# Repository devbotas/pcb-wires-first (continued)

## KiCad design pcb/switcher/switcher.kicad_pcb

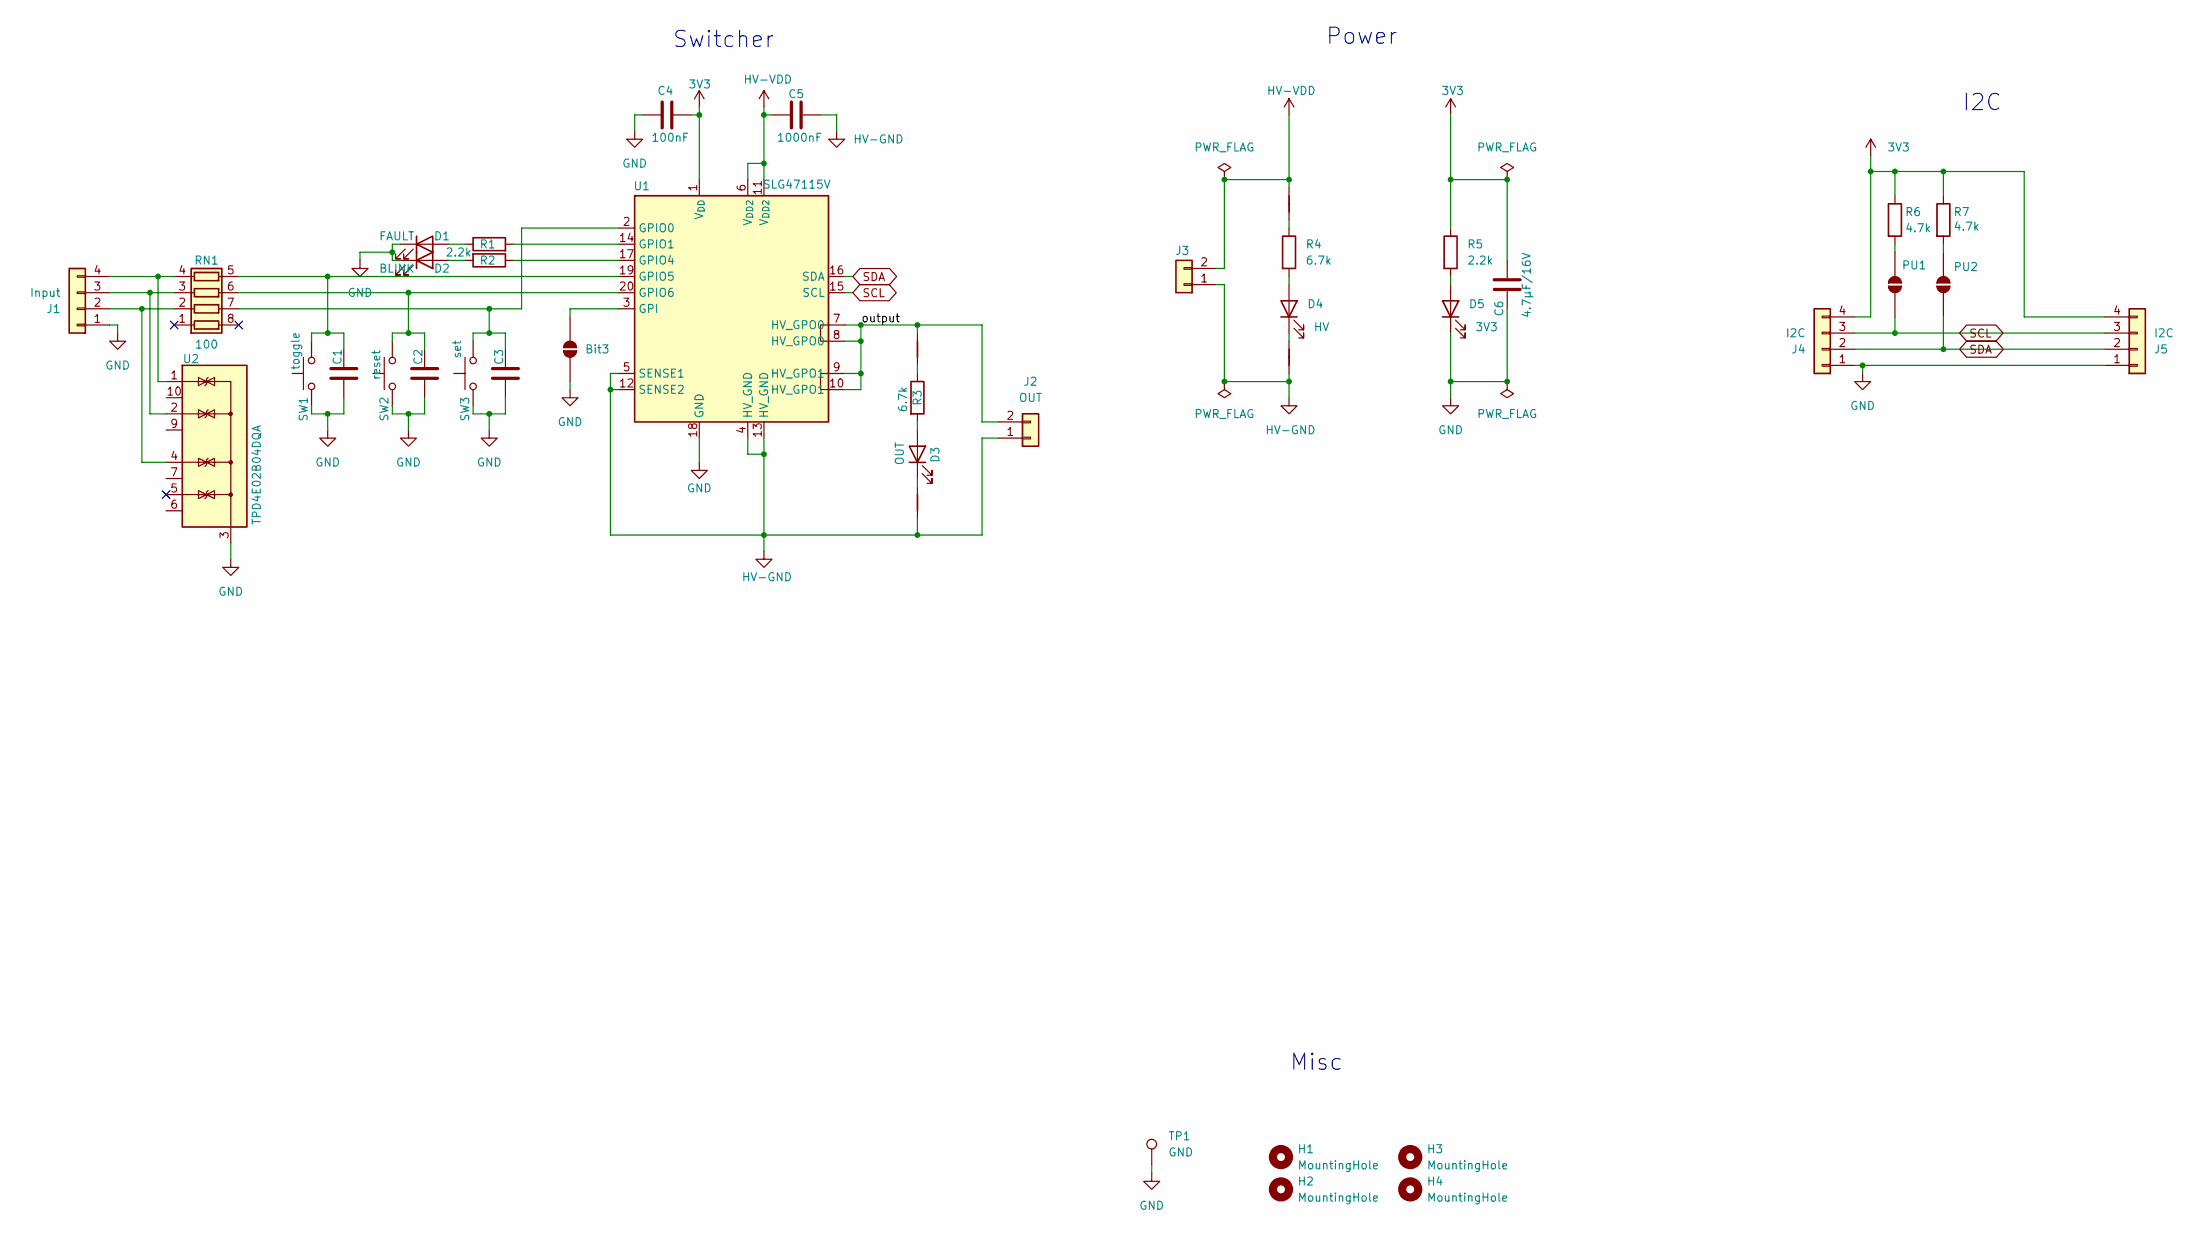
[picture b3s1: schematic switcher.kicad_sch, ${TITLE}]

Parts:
Bit3: SolderJumper_2_Open; SolderJumper-2_P1.3mm_Open_RoundedPad1.0x1.5mm
C1, C2, C3, C4: 100nF; C_0603_1608Metric
C5: 1000nF; C_0603_1608Metric
C6: 4.7μF/16V; C_0603_1608Metric
D1: FAULT; D_0603_1608Metric
D2: BLINK; D_0603_1608Metric
D3: OUT; D_0603_1608Metric
D4: HV; D_0603_1608Metric
D5: 3V3; D_0603_1608Metric
H1, H2, H3, H4: MountingHole; MountingHole_3.2mm_M3_NoCopper
J1: Input; PhoenixContact_MCV_1,5_4-G-3.5_1x04_P3.50mm_Vertical
J2: OUT; JST_VH_B2P-VH_1x02_P3.96mm_Vertical
J3: Conn_01x02; JST_VH_B2P-VH_1x02_P3.96mm_Vertical
J4, J5: I2C; JST_XH_B4B-XH-A_1x04_P2.50mm_Vertical
NT1, NT3, NT4: NetTie_2; NetTie-2_SMD_Pad0.5mm
NT2: NetTie_2; NetTie-2_THT_Pad0.3mm
PU1, PU2: SolderJumper_2_Open; SolderJumper-2_P1.3mm_Open_RoundedPad1.0x1.5mm
R1, R2, R5: 2.2k; R_0603_1608Metric
R3, R4: 6.7k; R_0603_1608Metric
R6, R7: 4.7k; R_0603_1608Metric
RN1: 100; R_Array_Concave_4x0603
SW1: toggle; SW_SPST_B3U-1000P
SW2: reset; SW_SPST_B3U-1000P
SW3: set; SW_SPST_B3U-1000P
TP1: GND; TestPoint_Keystone_5019_Miniature
U1: SLG47115V; Renesas_UQFN-20_2x3mm_P0.4mm_SLG47115V
U2: TPD4E02B04DQA; USON-10_2.5x1.0mm_P0.5mm

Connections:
3V3: C4.2, C6.1, J4.4, J5.4, R5.1, R6.1, R7.1, U1.1 (V_{DD})
/output: J2.2, NT1.2, U1.7 (HV_GPO0), U1.8 (HV_GPO0), U1.9 (HV_GPO1), U1.10 (HV_GPO1)
GND: Bit3.1 (A), C1.1, C2.1, C3.1, C4.1, C6.2, D1.1 (K), D2.1 (K), D5.1 (K), J1.1, J4.1, J5.1, SW1.1, SW2.1, SW3.1, TP1.1 (1_1), U1.18 (GND), U2.3 (G), U2.8 (G)
HV-GND: C5.1, J2.1, J3.1, NT2.1, NT4.1, U1.4 (HV_GND), U1.5 (SENSE1), U1.12 (SENSE2), U1.13 (HV_GND)
HV-VDD: C5.2, J3.2, NT3.2, U1.6 (V_{DD2}), U1.11 (V_{DD2})
unnamed: Bit3.2 (B), U1.3 (GPI)
unnamed: D1.2 (A), R1.1
unnamed: D2.2 (A), R2.2
unnamed: D3.2 (A), R3.2
unnamed: D3.1 (K), NT2.2
unnamed: D4.2 (A), R4.2
unnamed: D4.1 (K), NT4.2
unnamed: D5.2 (A), R5.2
unnamed: J1.2, RN1.2 (R2.1), U2.4 (IO3)
unnamed: J1.3, RN1.3 (R3.1), U2.2 (IO2)
unnamed: J1.4, RN1.4 (R4.1), U2.1 (IO1)
unnamed: NT1.1, R3.1
unnamed: NT3.1, R4.1
unnamed: PU1.2 (B), R6.2
unnamed: PU2.2 (B), R7.2
unnamed: C3.2, RN1.7 (R2.2), SW3.2, U1.2 (GPIO0)
unnamed: C2.2, RN1.6 (R3.2), SW2.2, U1.20 (GPIO6)
unnamed: C1.2, RN1.5 (R4.2), SW1.2, U1.19 (GPIO5)
unnamed: R1.2, U1.14 (GPIO1)
unnamed: R2.1, U1.17 (GPIO4)
SCL: J4.3, J5.3, PU1.1 (A), U1.15 (SCL)
SDA: J4.2, J5.2, PU2.1 (A), U1.16 (SDA)

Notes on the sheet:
Switcher
I2C
Power
Misc

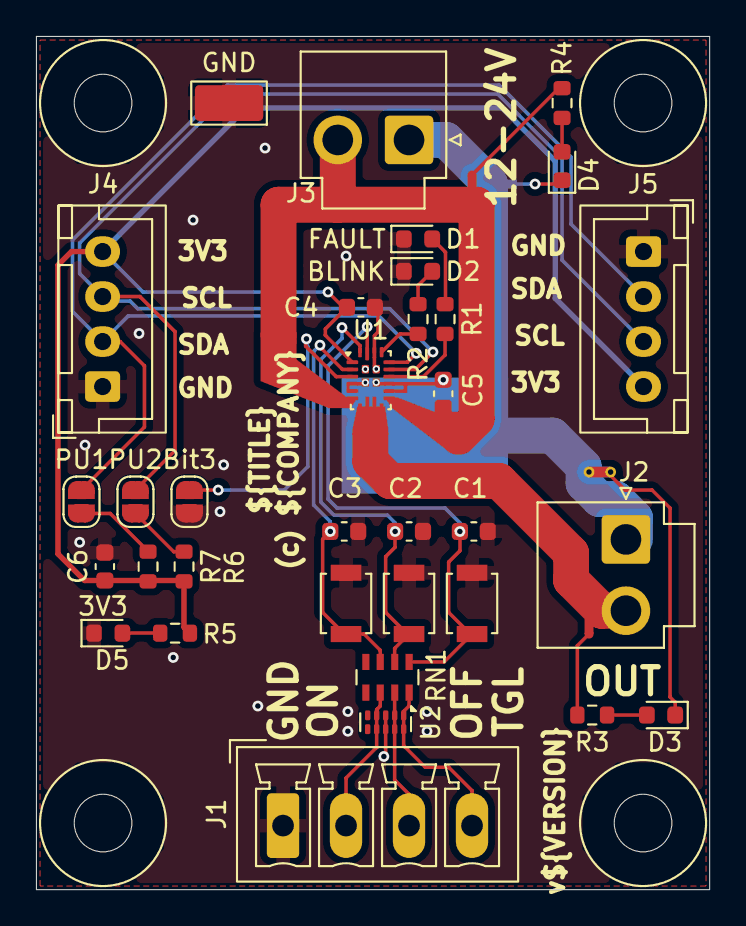
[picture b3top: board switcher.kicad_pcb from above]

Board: 2 copper layers, 37.4 x 47.4 mm, 41 parts (1 on the bottom side), 27 nets.

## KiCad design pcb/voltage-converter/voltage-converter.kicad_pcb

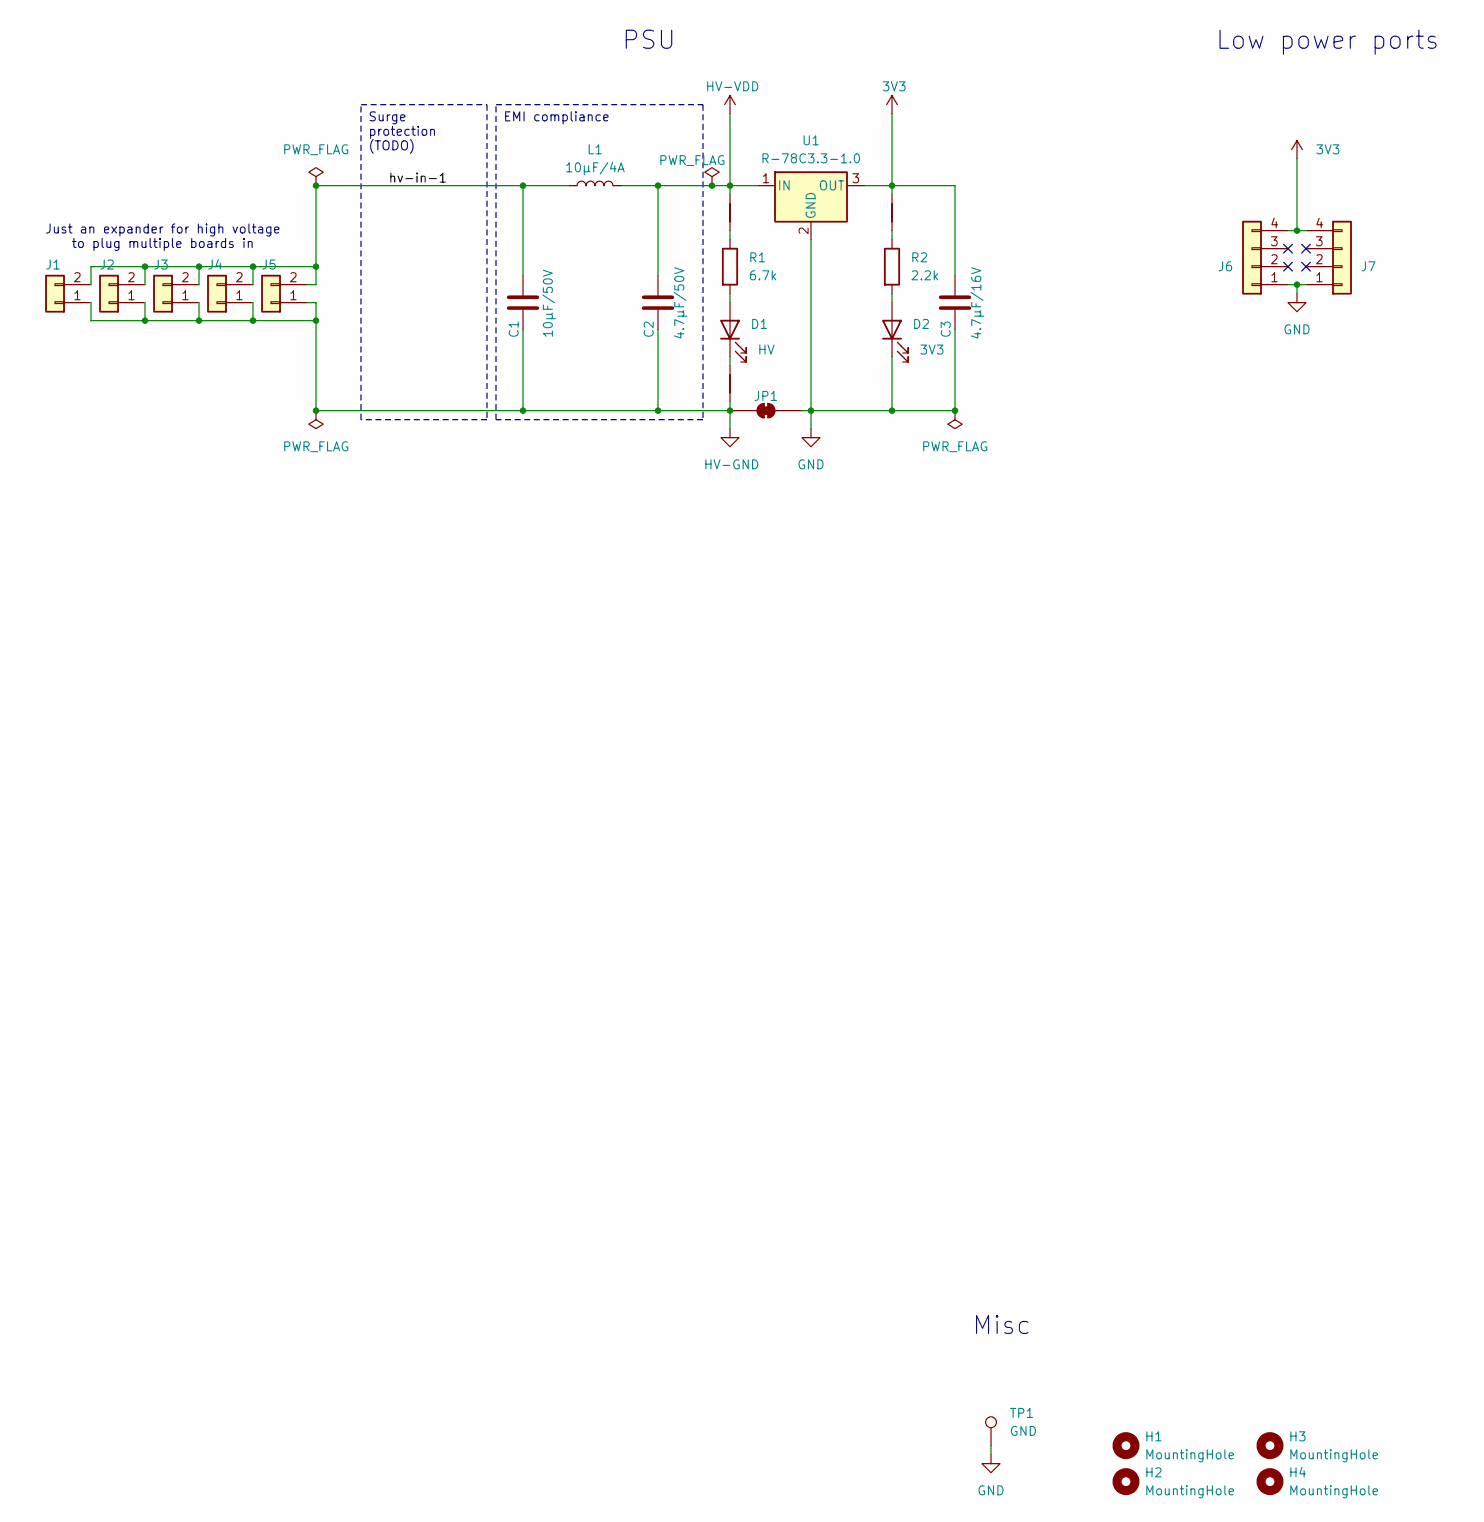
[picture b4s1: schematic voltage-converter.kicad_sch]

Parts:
C1: 10μF/50V; C_1206_3216Metric
C2: 4.7μF/50V; C_1206_3216Metric
C3: 4.7μF/16V; C_0603_1608Metric
D1: HV; D_0603_1608Metric
D2: 3V3; D_0603_1608Metric
H1, H2, H3, H4: MountingHole; MountingHole_3.2mm_M3_NoCopper
J1, J2, J3, J4, J5: Conn_01x02; JST_VH_B2P-VH_1x02_P3.96mm_Vertical
J6, J7: JST_XH_B4B-XH-A_1x04_P2.50mm_Vertical
JP1: SolderJumper_2_Bridged; SolderJumper-2_P1.3mm_Bridged_RoundedPad1.0x1.5mm
L1: 10μF/4A; L_Bourns_SRP7028A_7.3x6.6mm
NT1, NT2, NT3: NetTie_2; NetTie-2_SMD_Pad0.5mm
R1: 6.7k; R_0603_1608Metric
R2: 2.2k; R_0603_1608Metric
TP1: GND; TestPoint_Keystone_5019_Miniature
U1: R-78C3.3-1.0; Converter_DCDC_RECOM_R-78E-0.5_THT

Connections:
3V3: C3.1, J6.4, J7.4, NT3.2, U1.3 (OUT)
/hv-in-1: C1.1, J1.2, J2.2, J3.2, J4.2, J5.2, L1.1
GND: C3.2, D2.1 (K), J6.1, J7.1, JP1.2 (B), TP1.1 (1_1), U1.2 (GND)
HV-GND: C1.2, C2.2, J1.1, J2.1, J3.1, J4.1, J5.1, JP1.1 (A), NT2.1
HV-VDD: C2.1, L1.2, NT1.2, U1.1 (IN)
unnamed: D1.2 (A), R1.2
unnamed: D1.1 (K), NT2.2
unnamed: D2.2 (A), R2.2
unnamed: NT1.1, R1.1
unnamed: NT3.1, R2.1

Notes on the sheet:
Just an expander for high voltage to plug multiple boards in
Low power ports
PSU
Misc
Surge protection (TODO)
EMI compliance

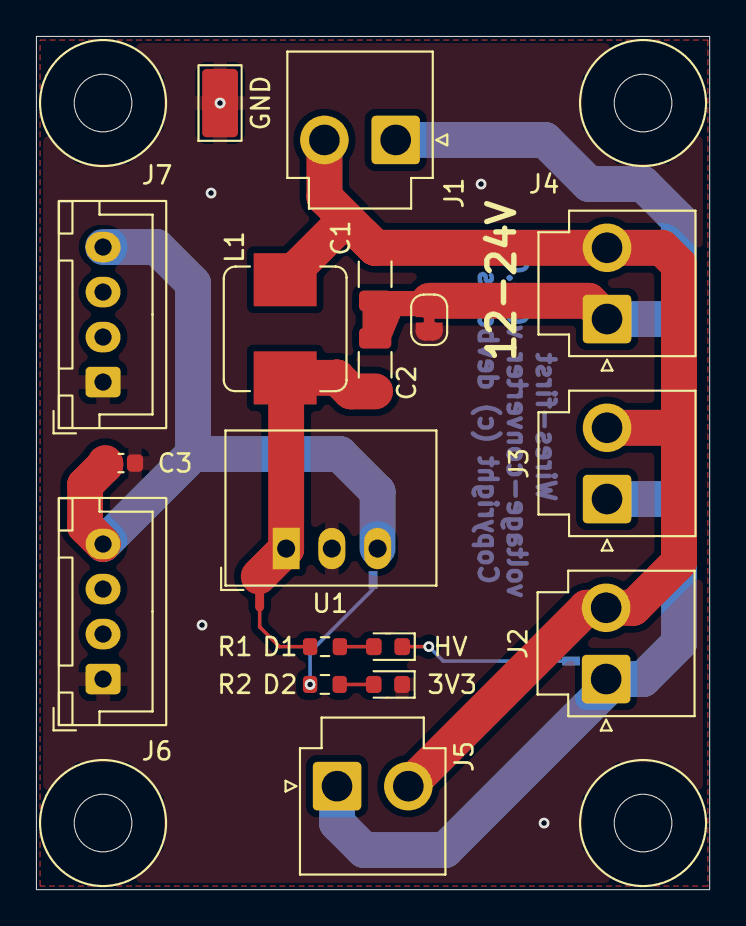
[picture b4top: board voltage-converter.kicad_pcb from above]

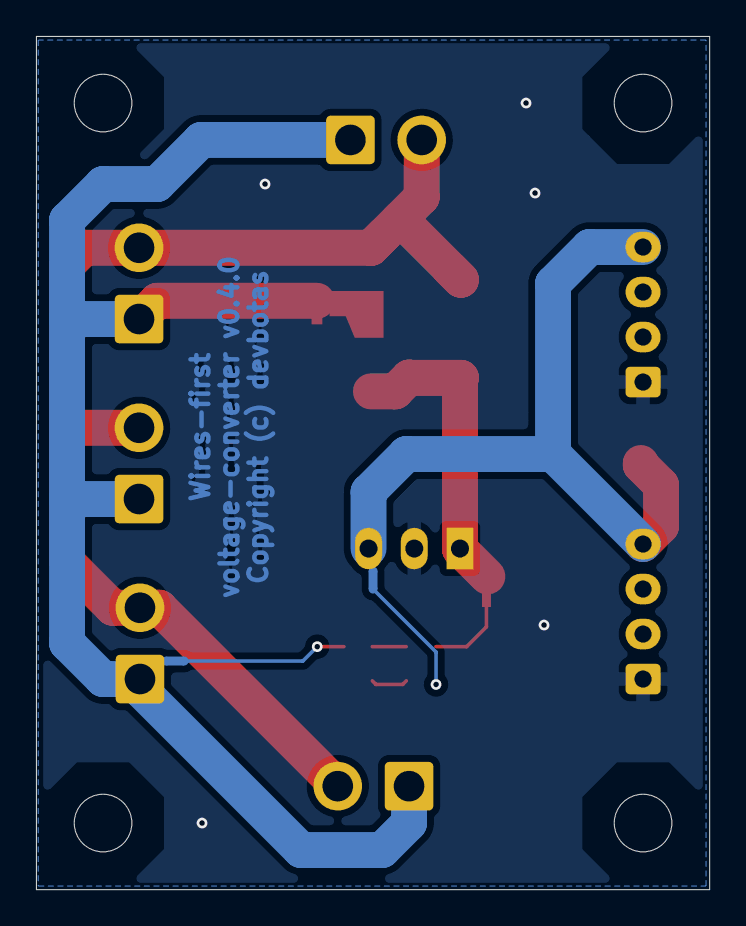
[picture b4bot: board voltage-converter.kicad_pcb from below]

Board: 2 copper layers, 37.4 x 47.4 mm, 25 parts (2 on the bottom side), 10 nets.

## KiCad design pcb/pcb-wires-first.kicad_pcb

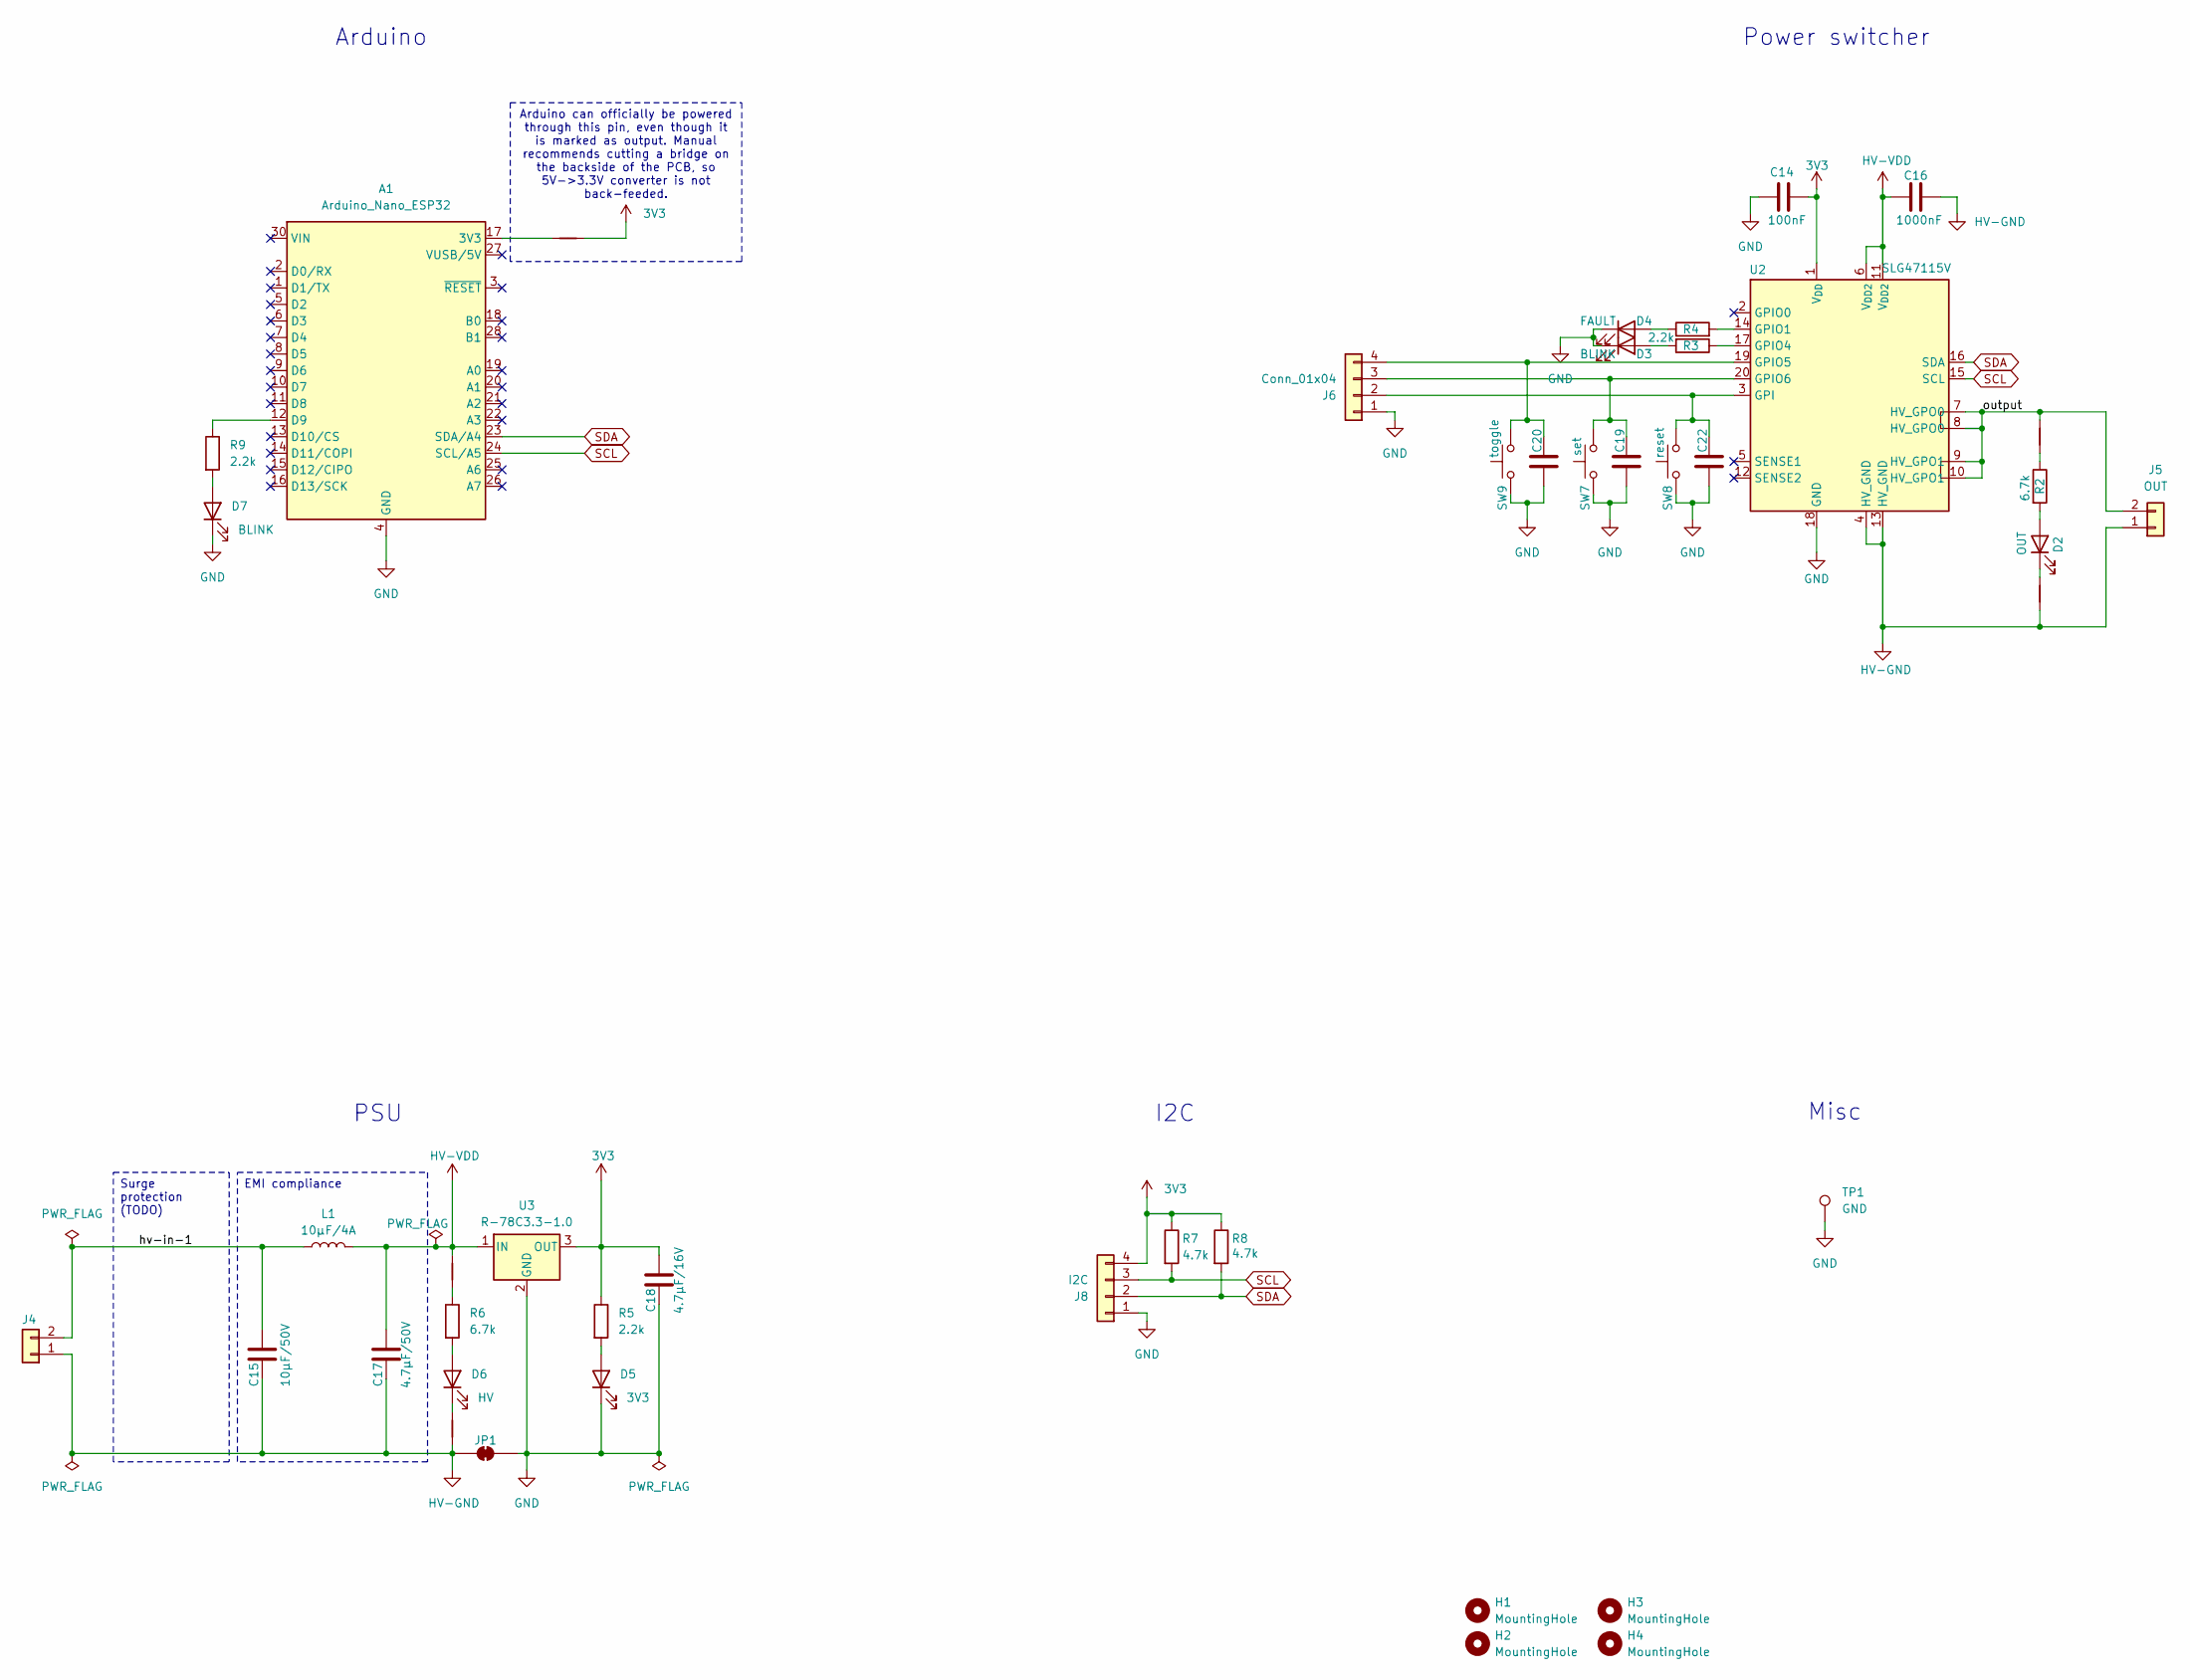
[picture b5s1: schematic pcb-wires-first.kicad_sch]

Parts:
A1: Arduino_Nano_ESP32; Arduino_Nano
C14, C19, C20, C22: 100nF; C_0603_1608Metric
C15: 10μF/50V; C_1206_3216Metric
C16: 1000nF; C_0603_1608Metric
C17: 4.7μF/50V; C_1206_3216Metric
C18: 4.7μF/16V; C_0603_1608Metric
D2: OUT; D_0603_1608Metric
D3, D7: BLINK; D_0603_1608Metric
D4: FAULT; D_0603_1608Metric
D5: 3V3; D_0603_1608Metric
D6: HV; D_0603_1608Metric
H1, H2, H3, H4: MountingHole; MountingHole_3.2mm_M3_NoCopper
J4: Conn_01x02; JST_VH_B2P-VH_1x02_P3.96mm_Vertical
J5: OUT; JST_VH_B2P-VH_1x02_P3.96mm_Vertical
J6: Conn_01x04; PhoenixContact_MCV_1,5_4-G-3.5_1x04_P3.50mm_Vertical
J8: I2C; JST_XH_B4B-XH-A_1x04_P2.50mm_Vertical
JP1: SolderJumper_2_Bridged; SolderJumper-2_P1.3mm_Bridged_RoundedPad1.0x1.5mm
L1: 10μF/4A; L_Bourns_SRP7028A_7.3x6.6mm
NT1, NT2, NT3, NT4: NetTie_2; NetTie-2_SMD_Pad0.5mm
NT5: NetTie_2; NetTie-2_THT_Pad0.3mm
R2, R6: 6.7k; R_0603_1608Metric
R3, R4, R5, R9: 2.2k; R_0603_1608Metric
R7, R8: 4.7k; R_0603_1608Metric
SW7: set; SW_SPST_B3U-1000P
SW8: reset; SW_SPST_B3U-1000P
SW9: toggle; SW_SPST_B3U-1000P
TP1: GND; TestPoint_Keystone_5019_Miniature
U2: SLG47115V; Renesas_UQFN-20_2x3mm_P0.4mm_LayoutBorder4x6y
U3: R-78C3.3-1.0; Converter_DCDC_RECOM_R-78E-0.5_THT

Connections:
3V3: C14.2, C18.1, J8.4, NT1.2, R5.1, R7.1, R8.1, U2.1 (V_{DD}), U3.3 (OUT)
/hv-in-1: C15.1, J4.2, L1.1
/output: J5.2, NT4.2, U2.7 (HV_GPO0), U2.8 (HV_GPO0), U2.9 (HV_GPO1), U2.10 (HV_GPO1)
GND: A1.4 (GND), A1.29 (GND), C14.1, C18.2, C19.1, C20.1, C22.1, D3.1 (K), D4.1 (K), D5.1 (K), D7.1 (K), J6.1, J8.1, JP1.2 (B), SW7.1, SW8.1, SW9.1, TP1.1 (1_1), U2.18 (GND), U3.2 (GND)
HV-GND: C15.2, C16.1, C17.2, J4.1, J5.1, JP1.1 (A), NT3.1, NT5.1, U2.4 (HV_GND), U2.13 (HV_GND)
HV-VDD: C16.2, C17.1, L1.2, NT2.2, U2.6 (V_{DD2}), U2.11 (V_{DD2}), U3.1 (IN)
unnamed: A1.17 (3V3), NT1.1
unnamed: A1.12 (D9), R9.1
unnamed: D2.2 (A), R2.2
unnamed: D2.1 (K), NT5.2
unnamed: D3.2 (A), R3.2
unnamed: D4.2 (A), R4.1
unnamed: D5.2 (A), R5.2
unnamed: D6.2 (A), R6.2
unnamed: D6.1 (K), NT3.2
unnamed: D7.2 (A), R9.2
unnamed: C22.2, J6.2, SW8.2, U2.3 (GPI)
unnamed: C19.2, J6.3, SW7.2, U2.20 (GPIO6)
unnamed: C20.2, J6.4, SW9.2, U2.19 (GPIO5)
unnamed: NT2.1, R6.1
unnamed: NT4.1, R2.1
unnamed: R4.2, U2.14 (GPIO1)
unnamed: R3.1, U2.17 (GPIO4)
SCL: A1.24 (SCL/A5), J8.3, R7.2, U2.15 (SCL)
SDA: A1.23 (SDA/A4), J8.2, R8.2, U2.16 (SDA)

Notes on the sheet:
Power switcher
I2C
PSU
Misc
Arduino
Arduino can officially be powered through this pin, even though it is marked as output. Manual recommends cutting a bridge on the backside of the PCB, so 5V->3.3V converter is not back-feeded.
Surge protection (TODO)
EMI compliance

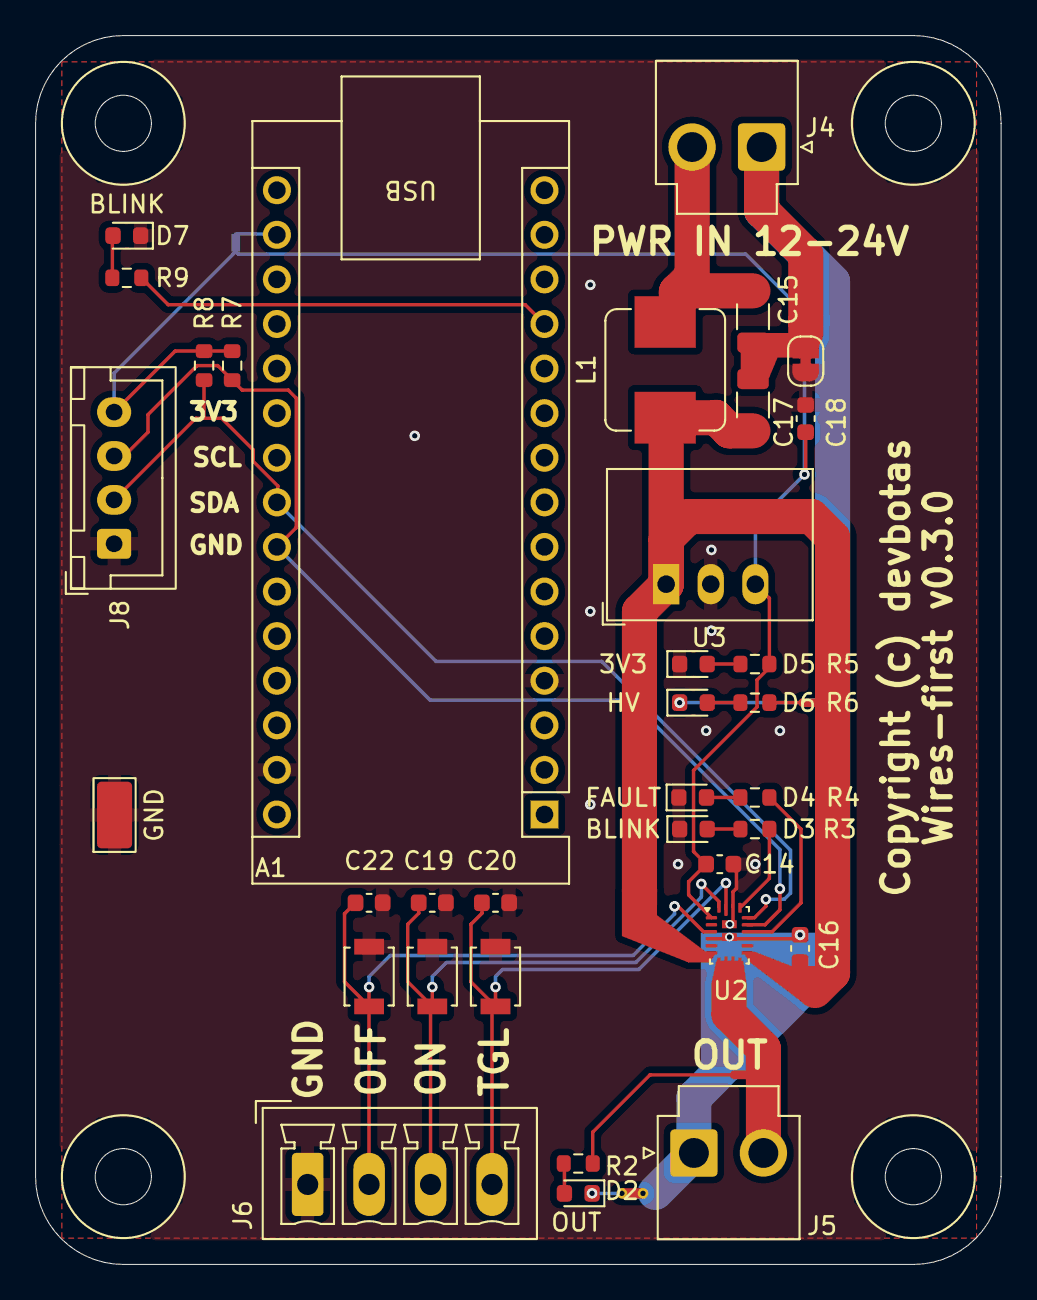
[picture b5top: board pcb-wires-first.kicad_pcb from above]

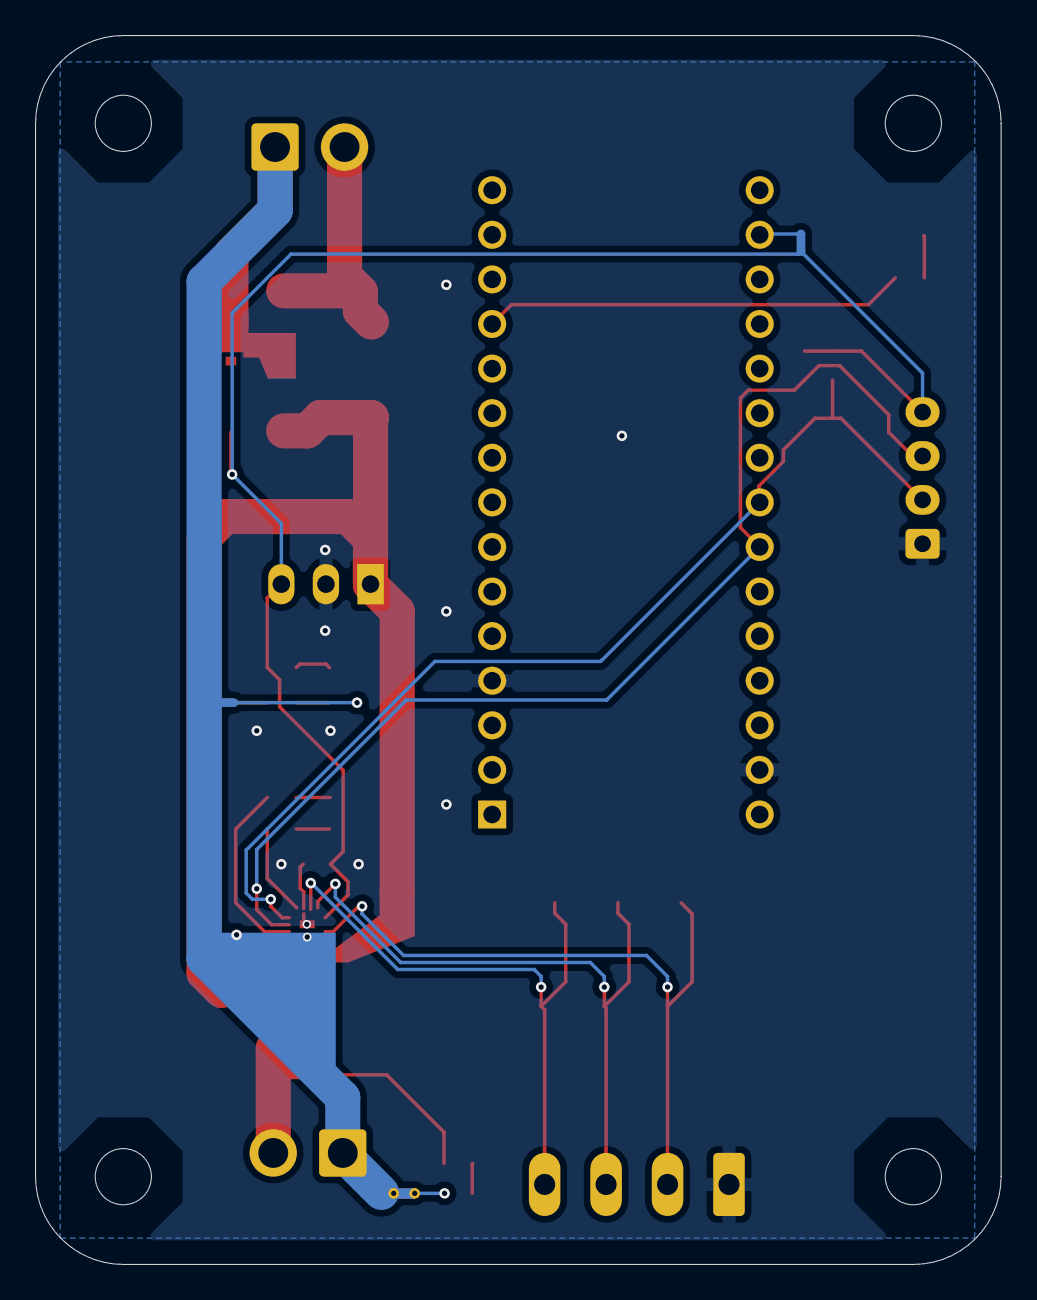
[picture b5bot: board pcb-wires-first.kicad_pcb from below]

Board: 2 copper layers, 55.0 x 70.0 mm, 44 parts (2 on the bottom side), 25 nets.

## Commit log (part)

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2026-04-30 Creating a SLG47115 symbol.
2026-04-30 Drafting.
2026-05-04 Adding SLG47105, SLG47115 and SLG46826 symbols.
2026-05-04 Drafting the board.
2026-05-05 WIP.
2026-05-05 Working on PSU part mostly.
2026-05-05 Getting rid of the warnings.
2026-05-05 Tidying up schematic.
2026-05-06 Routing the board.
2026-05-06 Manually overriding clearance of some of those QFN pads. They are too close. Footprint bug.
2026-05-06 More routing.
2026-05-06 Routed!
2026-05-11 Adding an I2C connector.
2026-05-11 Doing a draft release.
2026-05-19 Adding some readme.
2026-05-19 Repouring?..
2026-06-03 Adding a custom mounting hole footprint which excludes copper.
2026-06-03 Adding more testpoints.
2026-06-03 Some SLG footprint pads have exclusions zones quasi-overlap by 0.00001, so disabling these DRC violations.
2026-06-03 Vibe coding 3D model copyier to stock libraries app into existence.
2026-06-03 Fixing the vibe-coded app (manually).
2026-06-03 Temporary commiting the app execs.
2026-06-04 Moving model pusher into a separate project.
2026-06-04 Adjusting tracks.
2026-06-05 Adding notes for vNext.
2026-06-08 Completely reworking the entire thing. It is sinble-channel now.
2026-06-09 IO6 and IO7 are GPO on 46826
2026-06-09 Adding blinker for Arduino.
2026-06-09 Cleaning up DRC violations in PCB.
2026-06-09 Some more cleanup.
2026-06-09 Updating readme.
2026-06-10 Some fine tuning.
2026-06-10 Moar fine-tuning.
2026-06-24 Updating to new libs.
2026-06-24 Updating PCB.
